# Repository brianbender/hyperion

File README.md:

# Hyperion mini

original Hyperion circuit by devi ever

## why 
I wanted to put a fuzz circuit between the potentiometers of my jaguar's rhythm circuit. The hyperion proved ideal. This kicad schematic can be used to produce PCBs suitable for this task. 

## bom per circuit

Components you might already have if you're converting an existing rhythm circuit:
- 2x rhythm circuit potentiometers with roller knobs (see section below on values)
- 1x rhythm circuit roller knob bracket

Through hole components:
- 1x 1k resistor 
    - this will be mounted on the RC's tone pot for the pregain control
- 2x NPN transistors (i used mpsa18)
- 1x PNP transistor (i used 2n5087)

SMD components (all 1206 sized, for ease of hand-soldering)
- 4x 100n capacitor 
        - consider c0g caps if microphonics are a concern. i used x7r and liked the results
- 2x 10k resistors
- 2x 2.2M resistors

## rhythm circuit potentiometer values

You probably won't be able to use 100k potentiometers on the rhythm circuit bracket. Fender's rhythm circuit pots have weirdly small sized shafts, so if you're using official parts your options are either 1M or 50k. I used 2 x 50k, and thought it was fine. If you'd like to use 100k pots to exactly match the schematic, you will probably need to acquire an aftermarket rhythm circuit bracket with roller wheels that can accommodate standard sized potentiometer shafts. If you need to choose to use the stock 1M and 50k potentiometer values, you might want to audition whether you prefer having the higher value as your pre-gain or volume control.

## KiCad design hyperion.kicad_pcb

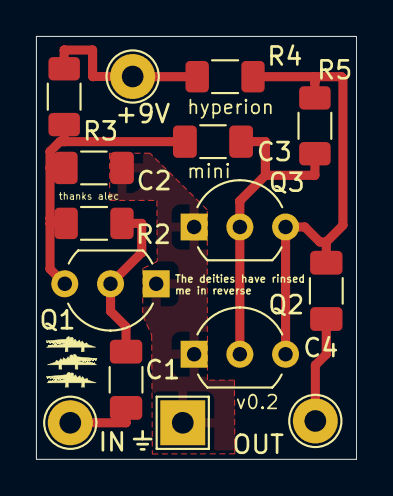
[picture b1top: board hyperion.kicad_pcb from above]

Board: 2 copper layers, 17.8 x 23.5 mm, 15 parts (0 on the bottom side), 8 nets.

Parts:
C1, C2, C3, C4: 100n; C_1206_3216Metric_Pad1.33x1.80mm_HandSolder
Q1, Q2: NPN; TO-92_Inline_Wide
Q3: PNP; TO-92_Inline_Wide
R2, R5: 2.2M; R_1206_3216Metric_Pad1.30x1.75mm_HandSolder
R3, R4: 10k; R_1206_3216Metric_Pad1.30x1.75mm_HandSolder
TP1: IN; TestPoint_THTPad_D2.5mm_Drill1.2mm
TP2: +9V; TestPoint_THTPad_D2.5mm_Drill1.2mm
TP3: ⏚; TestPoint_THTPad_2.5x2.5mm_Drill1.2mm
TP4: OUT; TestPoint_THTPad_D2.5mm_Drill1.2mm

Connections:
Earth: C2.2, Q1.1 (E), Q2.1 (E), Q3.1 (E), TP3.1
unnamed: C1.1, TP1.1
unnamed: C4.2, TP4.1
unnamed: C1.2, Q1.2 (B), R2.2
unnamed: C2.1, C3.1, Q1.3 (C), R2.1, R3.1
unnamed: C3.2, Q2.2 (B), Q3.2 (B), R5.2
unnamed: C4.1, Q2.3 (C), Q3.3 (C), R4.1, R5.1
unnamed: R3.2, R4.2, TP2.1

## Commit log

2025-02-20 correct the guitar wiring in the schematic
